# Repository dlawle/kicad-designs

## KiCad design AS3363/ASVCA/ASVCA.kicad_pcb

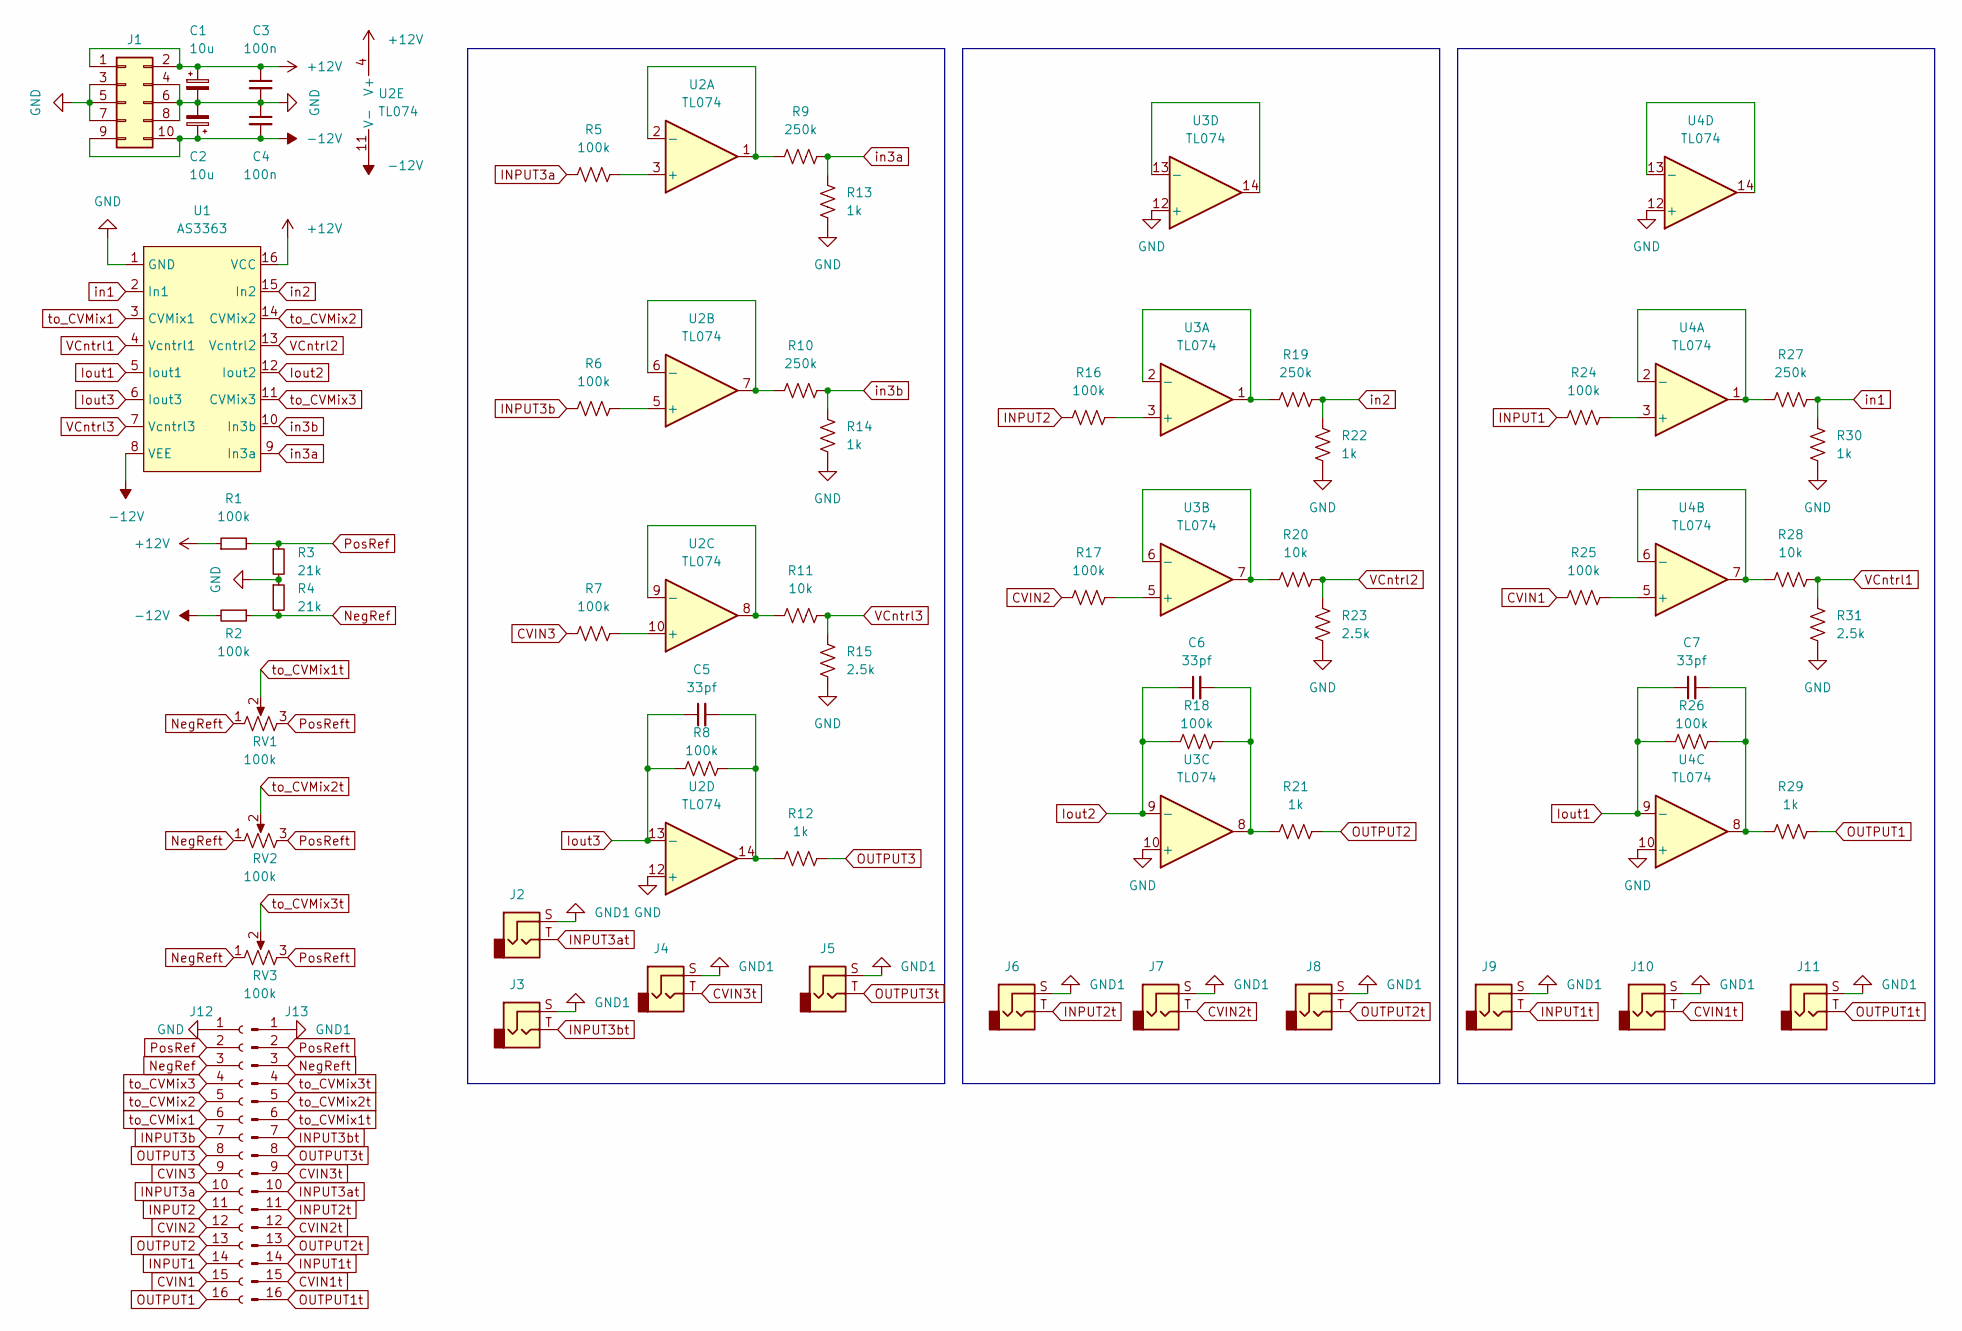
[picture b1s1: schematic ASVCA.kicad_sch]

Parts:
C1, C2: 10u; CP_Radial_D5.0mm_P2.50mm
C3, C4: 100n; C_Disc_D6.0mm_W2.5mm_P5.00mm
C5, C6, C7: 33pf; C_Disc_D6.0mm_W2.5mm_P5.00mm
J1: Conn_02x05_Counter_Clockwise; IDC-Header_2x05_P2.54mm_Vertical
J2: INPUT3a; AudioJack_3.5mm
J3: INPUT3b; AudioJack_3.5mm
J4: CVIN3; AudioJack_3.5mm
J5: OUTPUT3; AudioJack_3.5mm
J6: INPUT2; AudioJack_3.5mm
J7: CVIN2; AudioJack_3.5mm
J8: OUTPUT2; AudioJack_3.5mm
J9: INPUT1; AudioJack_3.5mm
J10: CVIN1; AudioJack_3.5mm
J11: OUTPUT1; AudioJack_3.5mm
J12: Conn_01x14_Female; PinHeader_1x16_P2.54mm_Vertical
J13: Conn_01x14_Male; PinHeader_1x16_P2.54mm_Vertical
R1, R2, R5, R6, R7, R8, R16, R17, R18, R24, R25, R26: 100k; Resistor_L6.3mm_D2.5mm_P7.62mm_Horizontal
R3, R4: 21k; Resistor_L6.3mm_D2.5mm_P7.62mm_Horizontal
R9, R10, R19, R27: 250k; Resistor_L6.3mm_D2.5mm_P7.62mm_Horizontal
R11, R20, R28: 10k; Resistor_L6.3mm_D2.5mm_P7.62mm_Horizontal
R12, R13, R14, R21, R22, R29, R30: 1k; Resistor_L6.3mm_D2.5mm_P7.62mm_Horizontal
R15, R23, R31: 2.5k; Resistor_L6.3mm_D2.5mm_P7.62mm_Horizontal
RV1, RV2, RV3: 100k; Potentiometer_RV09
U1: AS3363; DIP-16_W7.62mm_Socket
U2, U3, U4: TL074; DIP-14_W7.62mm_Socket

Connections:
+12V: C1.1, C3.1, J1.1, J1.2, R1.1, U1.16 (VCC), U2.4 (V+)
-12V: C2.1, C4.2, J1.9, J1.10, R2.2, U1.8 (VEE), U2.11 (V-)
CVIN1: J12.15, R25.1
CVIN1t: J10.T, J13.15
CVIN2: J12.12, R17.1
CVIN2t: J7.T, J13.12
CVIN3: J12.9, R7.1
CVIN3t: J4.T, J13.9
GND: C1.2, C2.2, C3.2, C4.1, J1.3, J1.4, J1.5, J1.6, J1.7, J1.8, J12.1, R3.2, R4.1, R13.1, R14.1, R15.1, R22.1, R23.1, R30.1, R31.1, U1.1 (GND), U2.12 (+), U3.10 (+), U3.12 (+), U4.10 (+), U4.12 (+)
GND1: J2.S, J3.S, J4.S, J5.S, J6.S, J7.S, J8.S, J9.S, J10.S, J11.S, J13.1
INPUT1: J12.14, R24.1
INPUT1t: J9.T, J13.14
INPUT2: J12.11, R16.1
INPUT2t: J6.T, J13.11
INPUT3a: J12.10, R5.1
INPUT3at: J2.T, J13.10
INPUT3b: J12.7, R6.1
INPUT3bt: J3.T, J13.7
Iout1: C7.1, R26.1, U1.5 (Iout1), U4.9 (-)
Iout2: C6.1, R18.1, U1.12 (Iout2), U3.9 (-)
Iout3: C5.1, R8.1, U1.6 (Iout3), U2.13 (-)
NegRef: J12.3, R2.1, R4.2
NegReft: J13.3, RV1.1, RV2.1, RV3.1
unnamed: C5.2, R8.2, R12.2, U2.14
unnamed: C6.2, R18.2, R21.2, U3.8
unnamed: C7.2, R26.2, R29.2, U4.8
unnamed: R5.2, U2.3 (+)
unnamed: R6.2, U2.5 (+)
unnamed: R7.2, U2.10 (+)
unnamed: R9.1, U2.1, U2.2 (-)
unnamed: R10.1, U2.6 (-), U2.7
unnamed: R11.1, U2.8, U2.9 (-)
unnamed: R16.2, U3.3 (+)
unnamed: R17.2, U3.5 (+)
unnamed: R19.1, U3.1, U3.2 (-)
unnamed: R20.1, U3.6 (-), U3.7
unnamed: R24.2, U4.3 (+)
unnamed: R25.2, U4.5 (+)
unnamed: R27.1, U4.1, U4.2 (-)
unnamed: R28.1, U4.6 (-), U4.7
unnamed: U3.13 (-), U3.14
unnamed: U4.13 (-), U4.14
OUTPUT1: J12.16, R29.1
OUTPUT1t: J11.T, J13.16
OUTPUT2: J12.13, R21.1
OUTPUT2t: J8.T, J13.13
OUTPUT3: J12.8, R12.1
OUTPUT3t: J5.T, J13.8
PosRef: J12.2, R1.2, R3.1
PosReft: J13.2, RV1.3, RV2.3, RV3.3
VCntrl1: R28.2, R31.2, U1.4 (Vcntrl1)
VCntrl2: R20.2, R23.2, U1.13 (Vcntrl2)
VCntrl3: R11.2, R15.2, U1.7 (Vcntrl3)
in1: R27.2, R30.2, U1.2 (In1)
in2: R19.2, R22.2, U1.15 (In2)
in3a: R9.2, R13.2, U1.9 (In3a)
in3b: R10.2, R14.2, U1.10 (In3b)
to_CVMix1: J12.6, U1.3 (CVMix1)
to_CVMix1t: J13.6, RV1.2
to_CVMix2: J12.5, U1.14 (CVMix2)
to_CVMix2t: J13.5, RV2.2
to_CVMix3: J12.4, U1.11 (CVMix3)
to_CVMix3t: J13.4, RV3.2

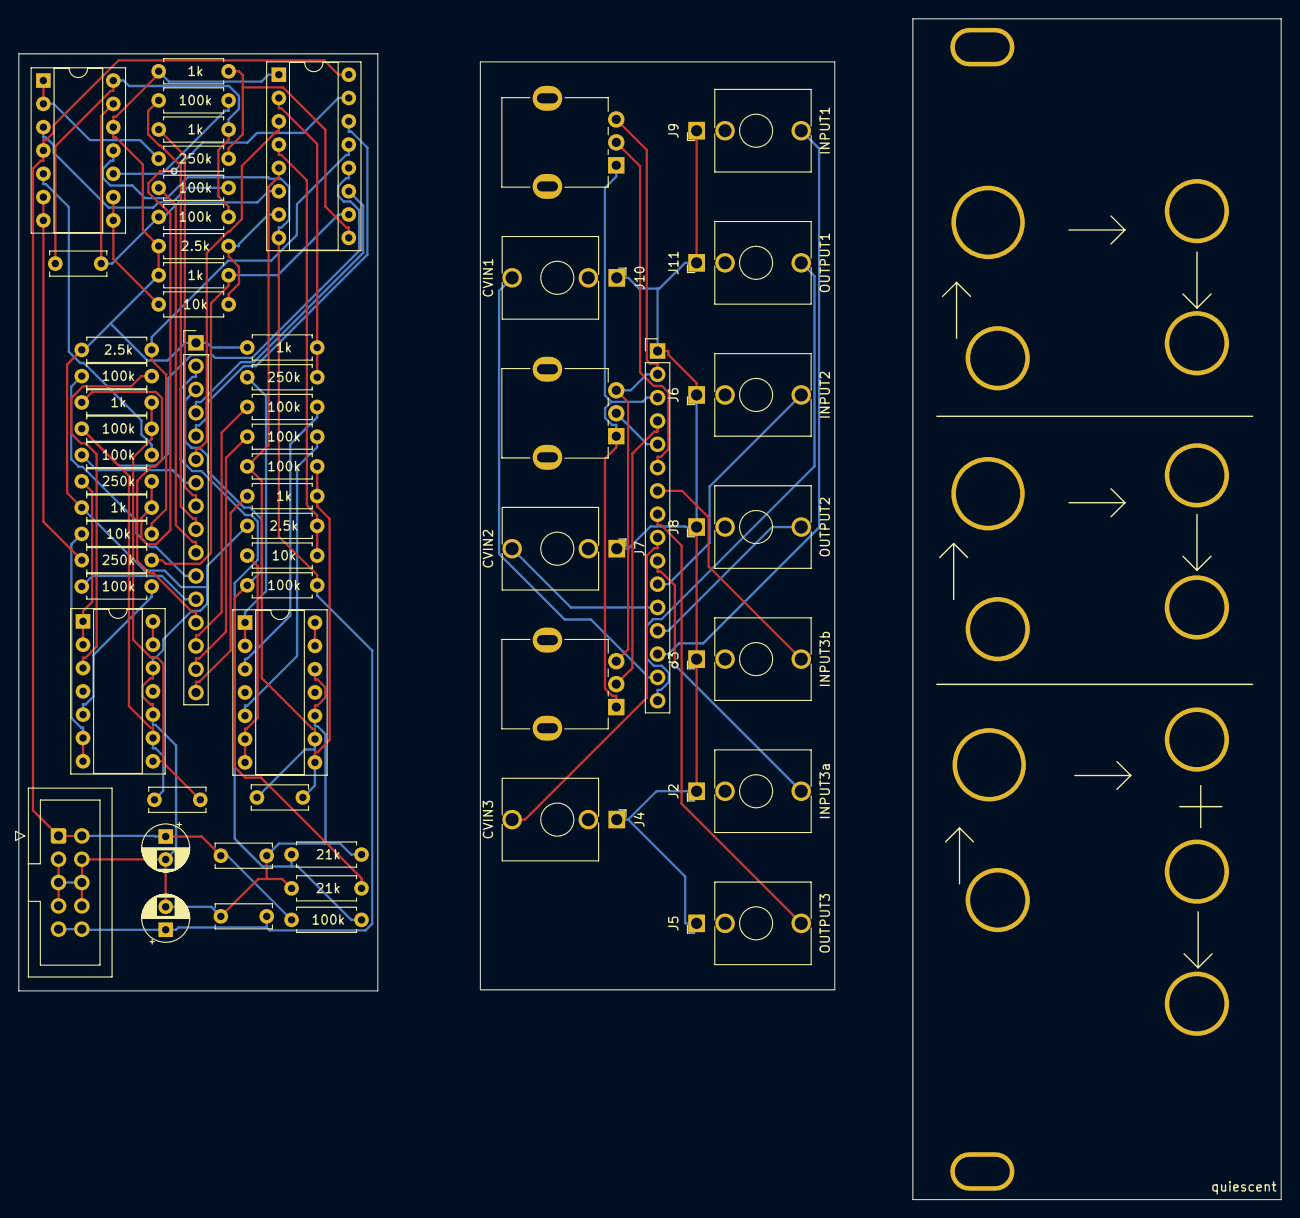
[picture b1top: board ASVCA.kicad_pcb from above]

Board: 2 copper layers, 137.5 x 128.7 mm, 68 parts (0 on the bottom side), 63 nets.

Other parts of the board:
-: PanelHole_AudioJack_3.5mm
-#2, -#3, -#4, -#5, -#6, -#7, -#8, -#9, -#10: PanelHole_AudioJack_3.5mm

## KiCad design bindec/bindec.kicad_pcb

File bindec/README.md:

A simple CMOS 555 clock with a CD4029 presettable up/down counter (binary and decade options)

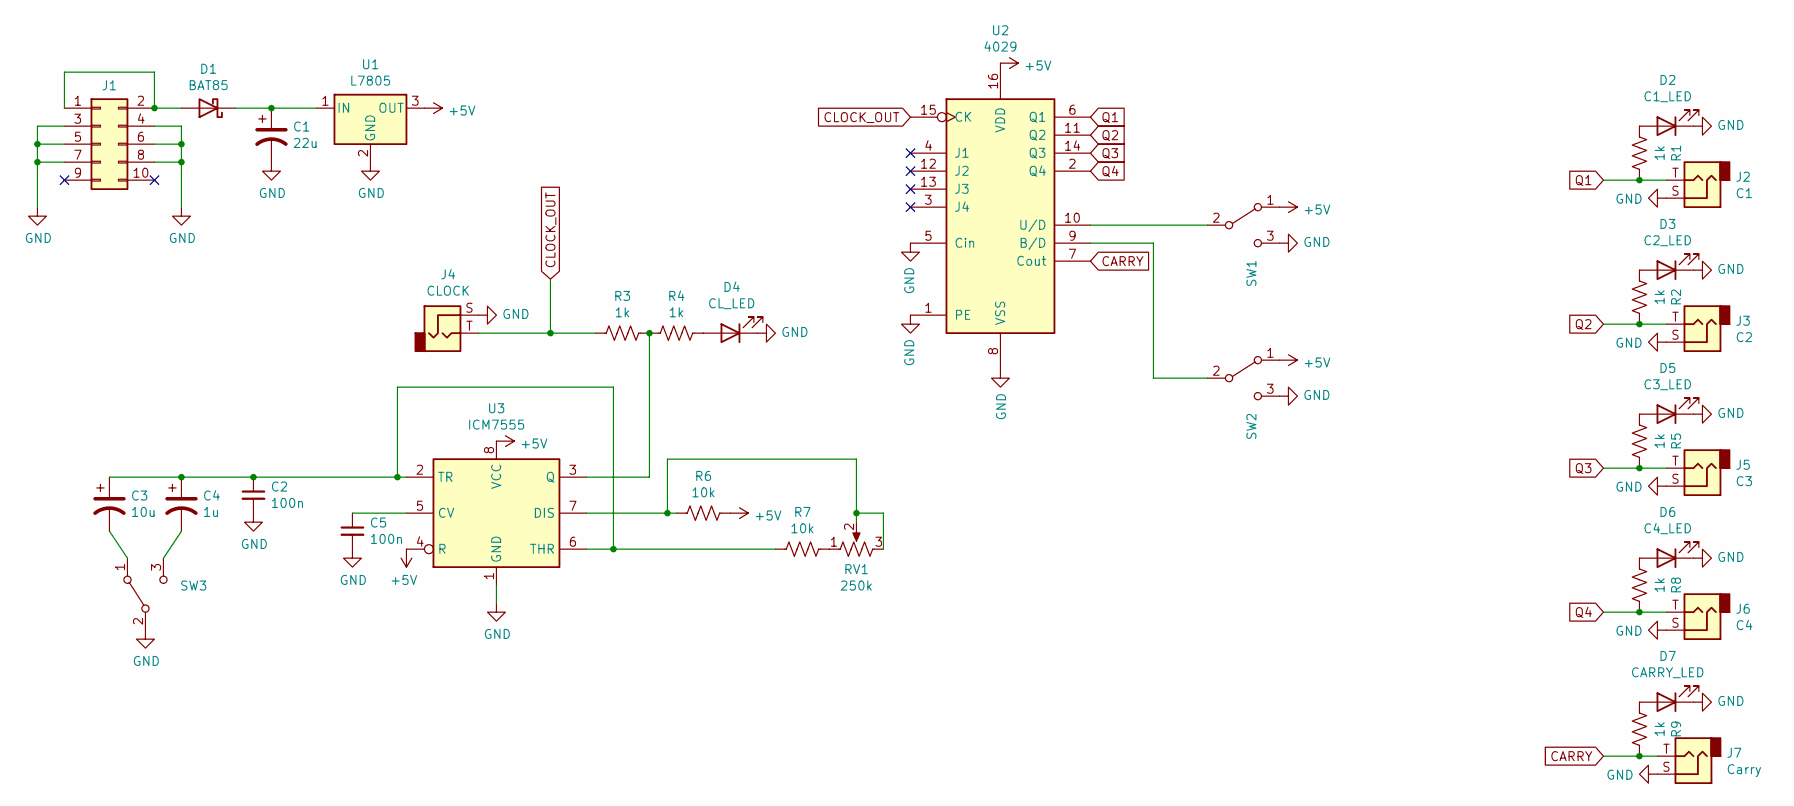
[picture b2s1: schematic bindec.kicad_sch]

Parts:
C1: 22u; Capacitor_Disc_D3.8mm_W2.6mm_P2.50mm
C2, C5: 100n; Capacitor_Disc_D3.8mm_W2.6mm_P2.50mm
C3: 10u; Capacitor_Radial_D5.0mm_P2.5mm
C4: 1u; Capacitor_Radial_D5.0mm_P2.5mm
D1: BAT85; D_DO-35_SOD27_P7.62mm_Horizontal
D2: C1_LED; LED_D3.0mm
D3: C2_LED; LED_D3.0mm
D4: CL_LED; LED_D3.0mm
D5: C3_LED; LED_D3.0mm
D6: C4_LED; LED_D3.0mm
D7: CARRY_LED; LED_D3.0mm
J1: Conn_02x05_Top_Bottom; IDC-Header_2x05_P2.54mm_Vertical
J2: C1; AudioJack_3.5mm
J3: C2; AudioJack_3.5mm
J4: CLOCK; AudioJack_3.5mm
J5: C3; AudioJack_3.5mm
J6: C4; AudioJack_3.5mm
J7: Carry; AudioJack_3.5mm
R1, R2, R3, R4, R5, R8, R9: 1k; Resistor_L6.3mm_D2.5mm_P7.62mm_Horizontal
R6, R7: 10k; Resistor_L6.3mm_D2.5mm_P7.62mm_Horizontal
RV1: 250k; Potentiometer_RV09
SW1, SW2, SW3: SW_SPDT; PinSocket_1x03_P2.54mm_Vertical
U1: L7805; TO-220-3_Vertical
U2: 4029; DIP-16_W7.62mm
U3: ICM7555; DIP-8_W7.62mm

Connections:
+5V: R6.1, SW1.1 (A), SW2.1 (A), U1.3 (OUT), U2.16 (VDD), U3.4 (R), U3.8 (VCC)
CARRY: J7.T, R9.1, U2.7 (Cout)
CLOCK_OUT: J4.T, R3.2, U2.15 (CK)
GND: C1.2, C2.2, C5.2, D2.1 (K), D3.1 (K), D4.1 (K), D5.1 (K), D6.1 (K), D7.1 (K), J1.3, J1.4, J1.5, J1.6, J1.7, J1.8, J2.S, J3.S, J4.S, J5.S, J6.S, J7.S, SW1.3 (C), SW2.3 (C), SW3.2 (B), U1.2 (GND), U2.1 (PE), U2.5 (Cin), U2.8 (VSS), U3.1 (GND)
unnamed: C1.1, D1.1 (K), U1.1 (IN)
unnamed: C2.1, C3.1, C4.1, R7.2, U3.2 (TR), U3.6 (THR)
unnamed: C3.2, SW3.1 (A)
unnamed: C4.2, SW3.3 (C)
unnamed: C5.1, U3.5 (CV)
unnamed: D1.2 (A), J1.1, J1.2
unnamed: D2.2 (A), R1.2
unnamed: D3.2 (A), R2.2
unnamed: D4.2 (A), R4.1
unnamed: D5.2 (A), R5.2
unnamed: D6.2 (A), R8.2
unnamed: D7.2 (A), R9.2
unnamed: R3.1, R4.2, U3.3 (Q)
unnamed: R6.2, RV1.2, RV1.3, U3.7 (DIS)
unnamed: R7.1, RV1.1
unnamed: SW1.2 (B), U2.10 (U/D)
unnamed: SW2.2 (B), U2.9 (B/D)
Q1: J2.T, R1.1, U2.6 (Q1)
Q2: J3.T, R2.1, U2.11 (Q2)
Q3: J5.T, R5.1, U2.14 (Q3)
Q4: J6.T, R8.1, U2.2 (Q4)

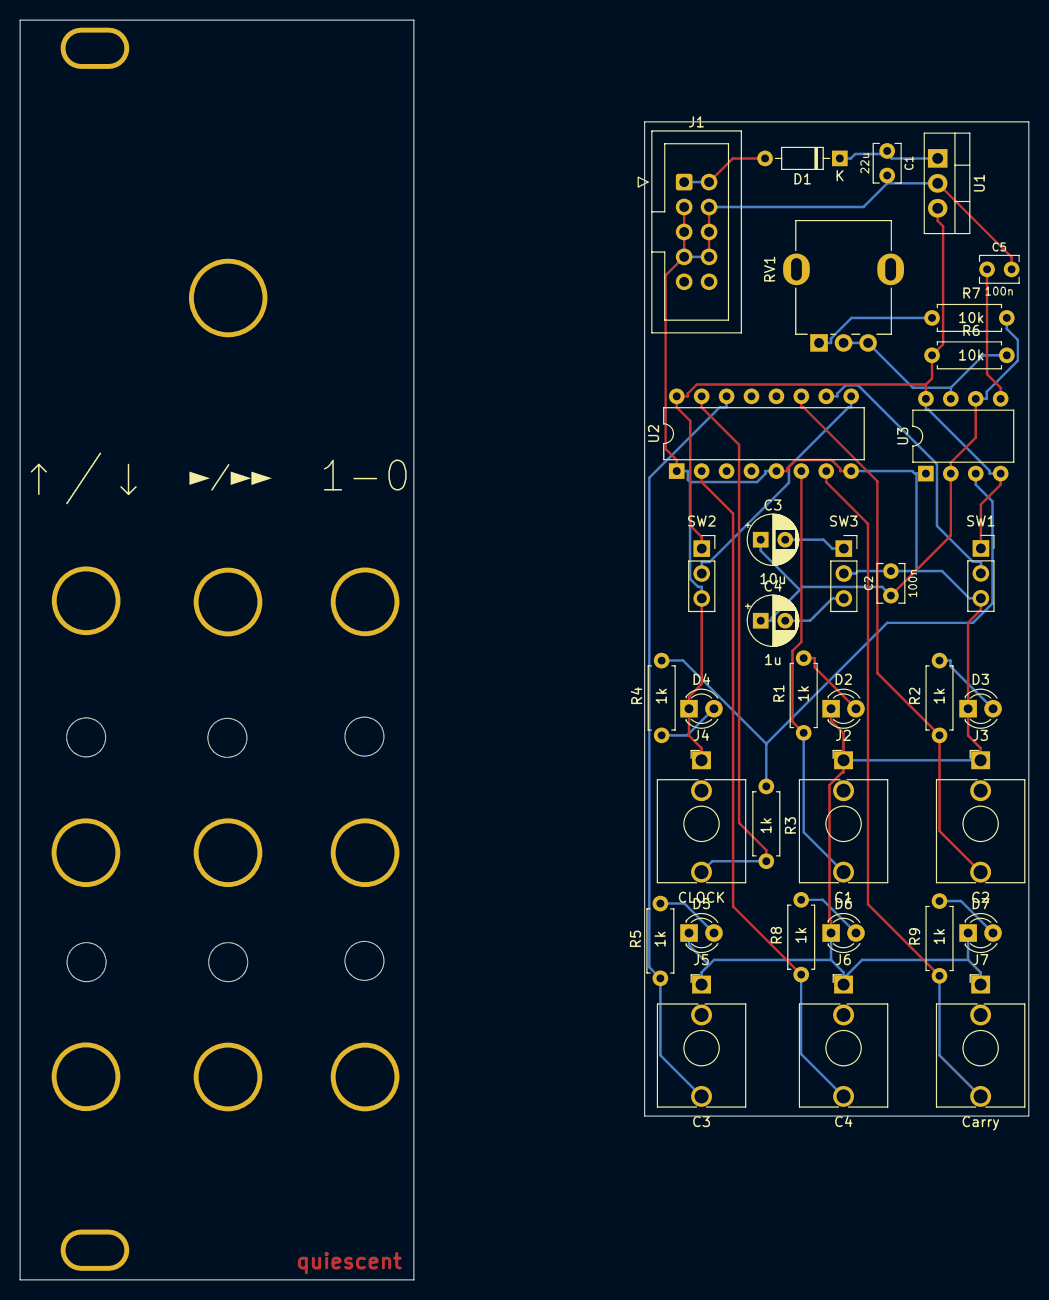
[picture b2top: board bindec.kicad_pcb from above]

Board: 2 copper layers, 102.8 x 128.4 mm, 35 parts (0 on the bottom side), 25 nets.

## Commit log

2022-09-29 Rename bindec.kicad_pcb to bindec/bindec.kicad_pcb
2022-09-29 Rename bindec.kicad_prl to bindec/bindec.kicad_prl
2022-09-29 Rename bindec.kicad_sch to bindec/bindec.kicad_sch
2022-09-29 Rename bindec.kicad_pro to bindec/bindec.kicad_pro
2022-10-05 updating designs
2022-10-17 updating gerbers
